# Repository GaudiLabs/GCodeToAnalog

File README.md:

# GCodeToAnalog
grbl-arduino_micro based Gcode to Analog converter circuit and code

Modified the code and added analog out commands for circuit with digital to analog converter (DAC) MCP4922-E. Can be used to control analog pen printers by sending gcode. 

Based on:
https://github.com/rdpowers/grbl/blob/atmega32u4-support-8c/COPYING

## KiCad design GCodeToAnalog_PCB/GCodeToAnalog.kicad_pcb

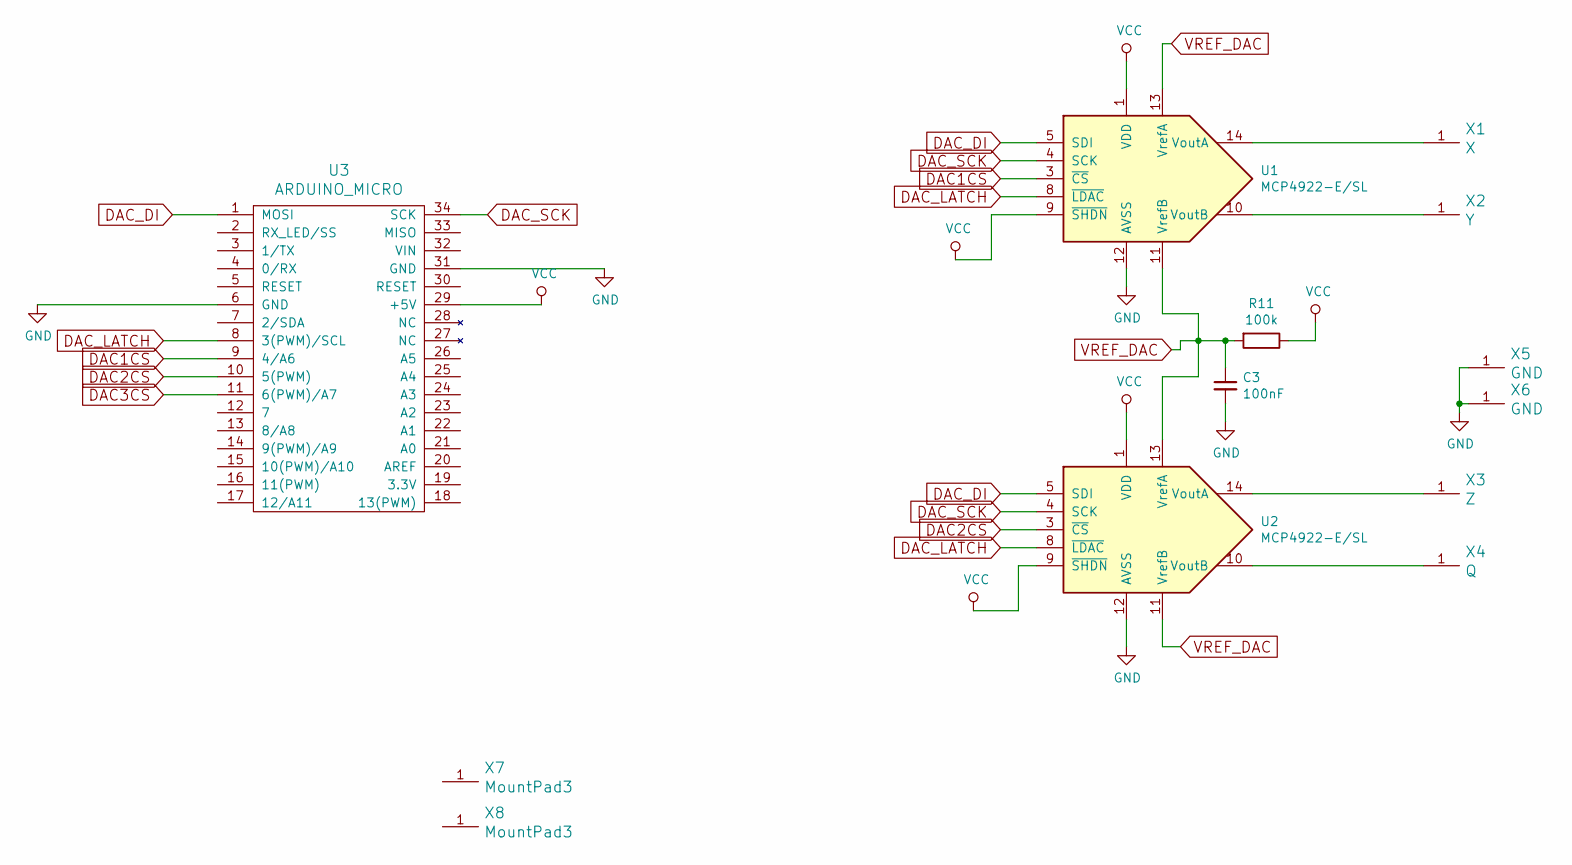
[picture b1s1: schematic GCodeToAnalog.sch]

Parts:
C3: 100nF; 0805G
R11: 100k; 0805G
U1, U2: MCP4922-E/SL; SOIC-14_N
U3: ARDUINO_MICRO; Arduino_Micro_Throughole
X1: X; Pad4x8
X2: Y; Pad4x8
X3: Z; Pad4x8
X4: Q; Pad4x8
X5, X6: GND; Pad4x8
X7, X8: MountPad3; MountingHoleM3

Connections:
DAC1CS: U1.3 (~CS~), U3.9 (4/A6)
DAC2CS: U2.3 (~CS~), U3.10 (5(PWM))
DAC3CS: U3.11 (6(PWM)/A7)
DAC_DI: U1.5 (SDI), U2.5 (SDI), U3.1 (MOSI)
DAC_LATCH: U1.8 (~LDAC~), U2.8 (~LDAC~), U3.8 (3(PWM)/SCL)
DAC_SCK: U1.4 (SCK), U2.4 (SCK), U3.34 (SCK)
GND: C3.2, U1.12 (AVSS), U2.12 (AVSS), U3.6 (GND), U3.31 (GND), X5.1, X6.1
unnamed: U1.10 (VoutB), X2.1
unnamed: U1.14 (VoutA), X1.1
unnamed: U2.10 (VoutB), X4.1
unnamed: U2.14 (VoutA), X3.1
VCC: R11.1, U1.1 (VDD), U1.9 (~SHDN~), U2.1 (VDD), U2.9 (~SHDN~), U3.29 (+5V)
VREF_DAC: C3.1, R11.2, U1.11 (VrefB), U1.13 (VrefA), U2.11 (VrefB), U2.13 (VrefA)

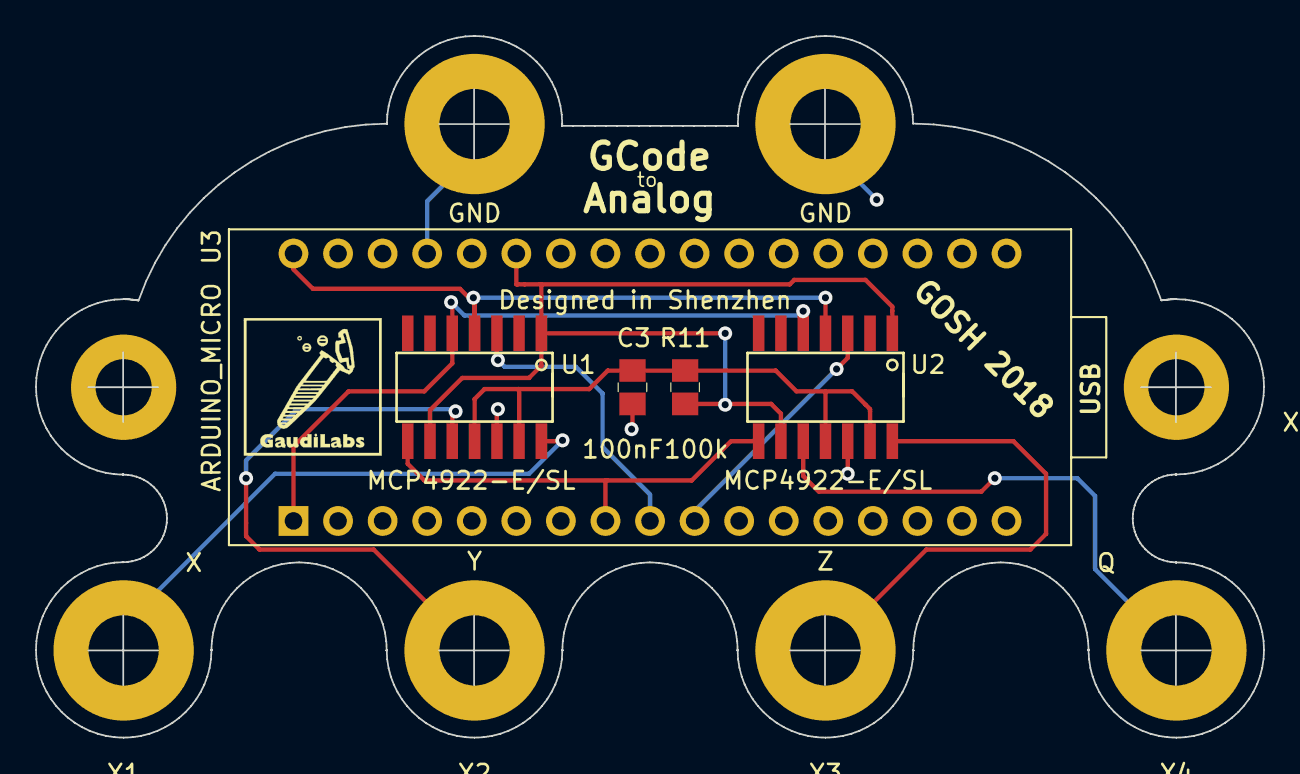
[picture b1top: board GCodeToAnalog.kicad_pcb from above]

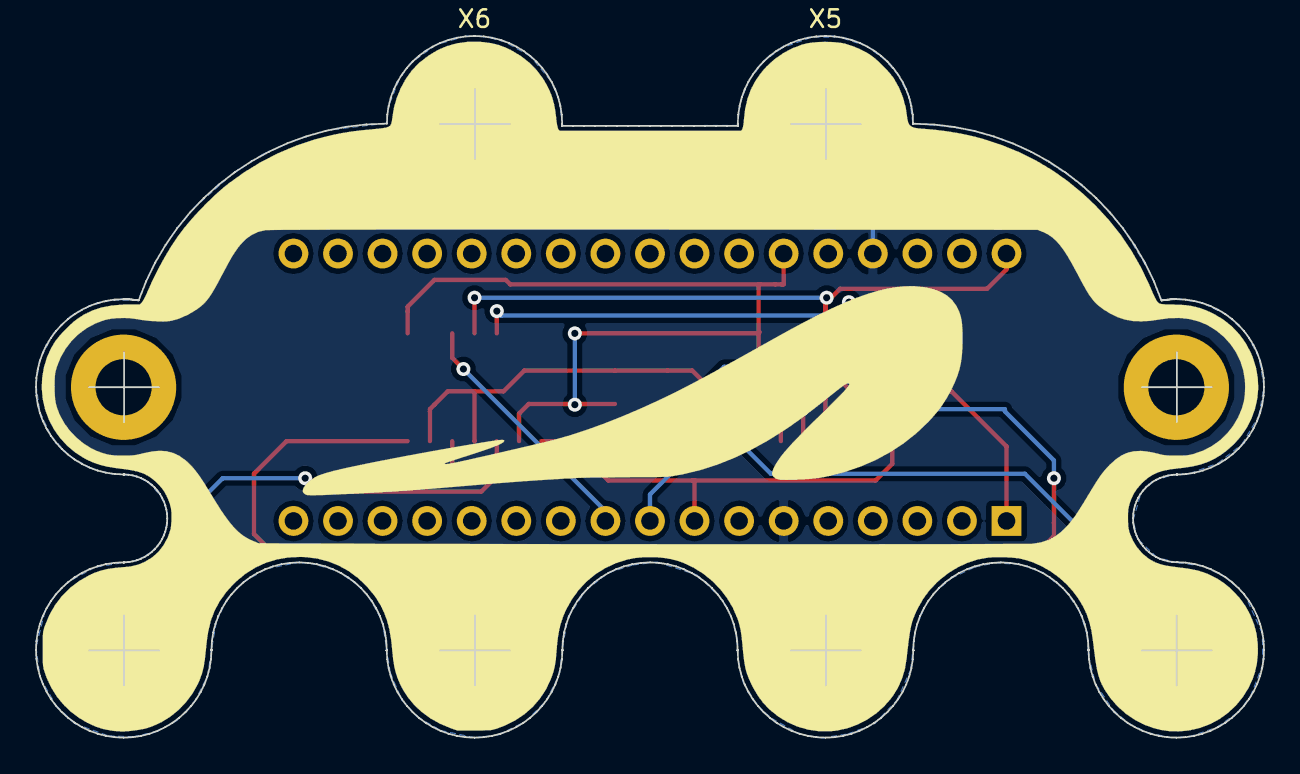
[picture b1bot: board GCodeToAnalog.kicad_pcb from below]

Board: 2 copper layers, 70.0 x 40.0 mm, 13 parts (3 on the bottom side), 12 nets.

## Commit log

2018-10-07 First Upload Just got the PCBs in Shenzhen, have to test now.
2018-10-30 Swaped Chanels X/Y Added hex file
2020-03-04 modified STEPS_PER_MM in defaults.h and recompiled
